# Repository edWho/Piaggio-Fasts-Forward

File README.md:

# Piaggio-Fasts-Forward
KiCAD test - Op Amp desgin

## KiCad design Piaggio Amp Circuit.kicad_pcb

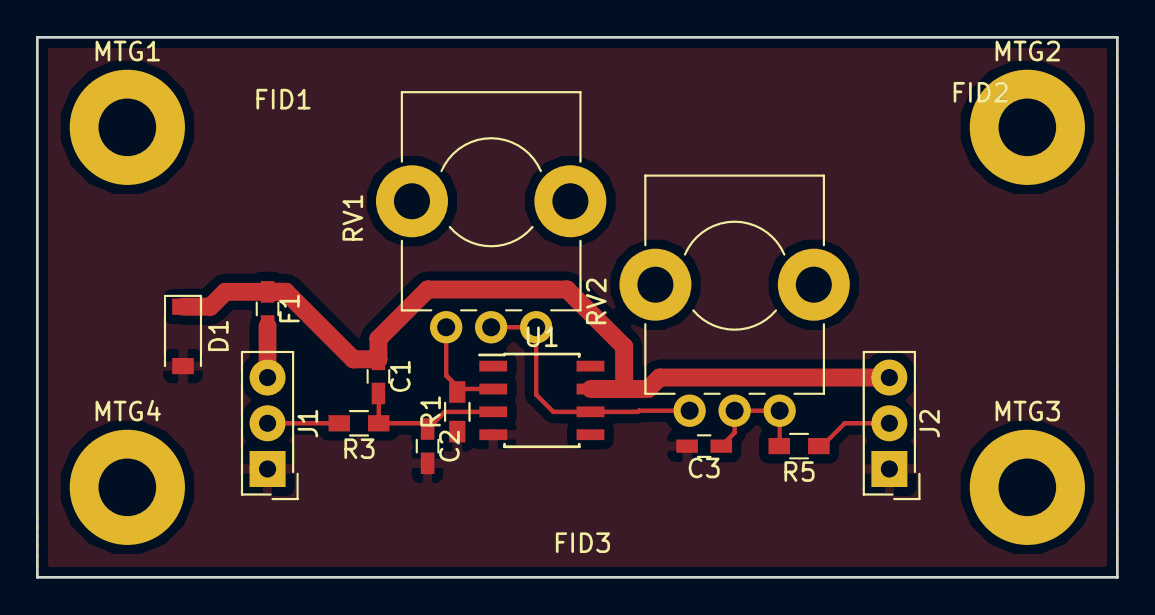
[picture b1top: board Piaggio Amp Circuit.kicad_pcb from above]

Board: 2 copper layers, 60.0 x 30.0 mm, 20 parts (0 on the bottom side), 9 nets.

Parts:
C1, C2: 0.01nF; C_0603_HandSoldering
C3: 0.1nF; C_0603_HandSoldering
D1: 20V 500mA; D_SOD-123
F1: 250mA; C_0603_HandSoldering
FID1, FID2, FID3: Fiducial_1mm_Dia_2.54mm_Outer_CopperBottom
J1, J2: M20-9990345; SL-103-X-XX_1x03
MTG1, MTG2, MTG3, MTG4: MountingHole_3.2mm_M3_Pad
R1: 3.3k; R_0603_HandSoldering
R3: 0; R_0603_HandSoldering
R5: 49.9; R_0603_HandSoldering
RV1, RV2: 5k; Potentiometer_Alps_RK09K_Horizontal
U1: OPA340UA; SOIC-8_3.9x4.9mm_Pitch1.27mm

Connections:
/5V: C1.1, D1.1, F1.1, J2.3, U1.7
/Vin: J1.2, R3.2
/Vout: RV1.1, RV1.2, RV2.3, U1.6
/Vout_FLT: C3.1, R5.2, RV2.1, RV2.2
GND: C2.2, C3.2, D1.2, J1.1, J2.1, R1.1, U1.4
unnamed: C1.2, C2.1, R3.1, U1.3
unnamed: F1.2, J1.3
unnamed: J2.2, R5.1
unnamed: R1.2, RV1.3, U1.2

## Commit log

2017-07-29 Add files via upload
    Piaggio Fast Forwrd KiCAD Op Amp Design Test
